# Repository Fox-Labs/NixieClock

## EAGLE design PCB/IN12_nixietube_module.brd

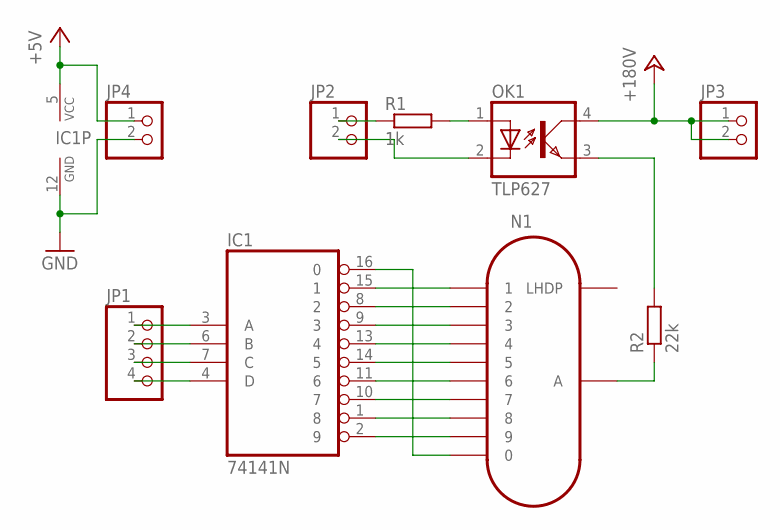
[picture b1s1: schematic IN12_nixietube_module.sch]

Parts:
IC1: 74141N; DIL16
JP1: PINHD-1X4; 1X04
JP2, JP3, JP4: PINHD-1X2; 1X02
N1: IN-12B; IN-12
OK1: TLP627; 4-SMD
R1: 1k; R0805
R2: 22k; 0207/10

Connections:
+5V: IC1.5 (VCC), JP4.1
+180V: JP3.1, JP3.2, OK1.4 (COL)
A: IC1.3 (A), JP1.1
B: IC1.6 (B), JP1.2
C: IC1.7 (C), JP1.3
C0: IC1.16 (0), N1.0
C1: IC1.15 (1), N1.1
C2: IC1.8 (2), N1.2
C3: IC1.9 (3), N1.3
C4: IC1.13 (4), N1.4
C5: IC1.14 (5), N1.5
C6: IC1.11 (6), N1.6
C7: IC1.10 (7), N1.7
C8: IC1.1 (8), N1.8
C9: IC1.2 (9), N1.9
D: IC1.4 (D), JP1.4
GND: IC1.12 (GND), JP4.2
LA: JP2.1, R1.1
LK: JP2.2, OK1.2 (C)
unnamed: N1.A, R2.1
unnamed: OK1.3 (EMIT), R2.2
unnamed: OK1.1 (A), R1.2

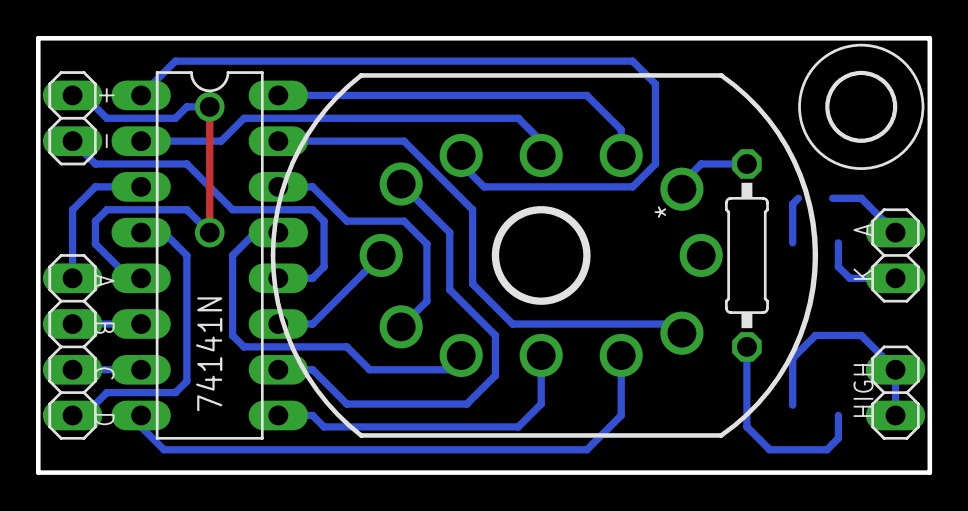
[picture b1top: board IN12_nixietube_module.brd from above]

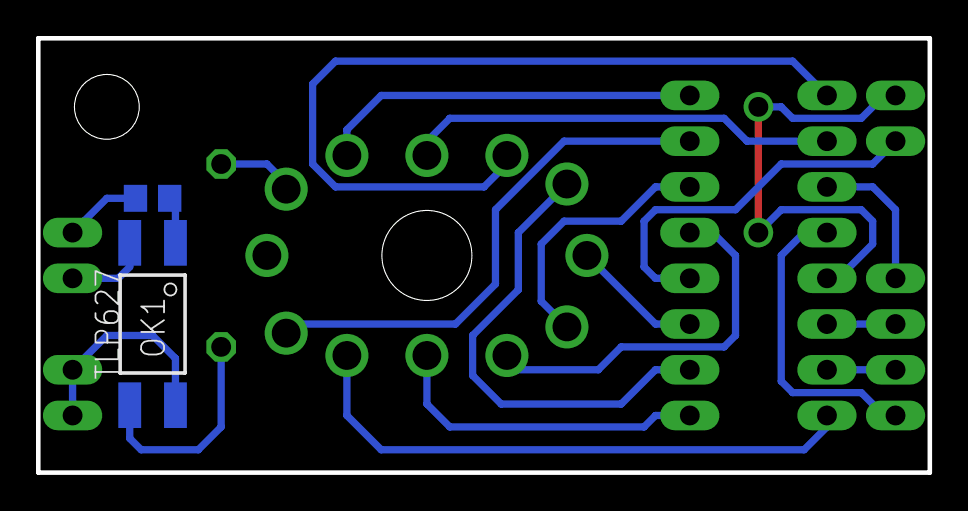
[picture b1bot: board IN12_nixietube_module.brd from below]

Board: 2 copper layers, 49.5 x 24.1 mm, 10 parts (2 on the bottom side), 22 nets.

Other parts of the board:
U$1: 3,6

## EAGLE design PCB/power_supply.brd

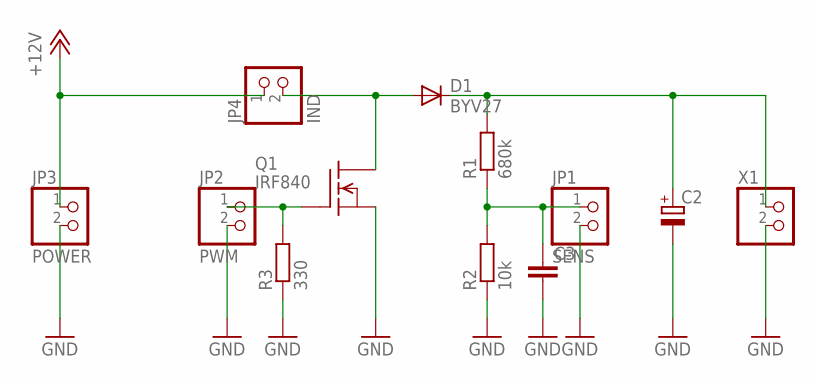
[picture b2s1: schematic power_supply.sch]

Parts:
C2: CPOL-EUE5-10,5; E5-10,5
C3: C-EU102-043X133; C102-043X133
D1: BYV27; SOD57
JP1: SENS; 1X02
JP2: PWM; 1X02
JP3: POWER; 1X02
JP4: IND; 1X02
Q1: IRF840; TO220-A
R1: 680k; 0207/7
R2: 10k; 0207/7
R3: 330; 0207/7
X1: W237-102

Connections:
180: C2.+, D1.C, R1.2, X1.1
+12V: JP3.1, JP4.1
GND: C2.-, C3.2, JP1.2, JP2.2, JP3.2, Q1.3 (S), R2.1, R3.1, X1.2
IND: D1.A, JP4.2, Q1.2 (D)
PWM: JP2.1, Q1.1 (G), R3.2
SENS: C3.1, JP1.1, R1.1, R2.2

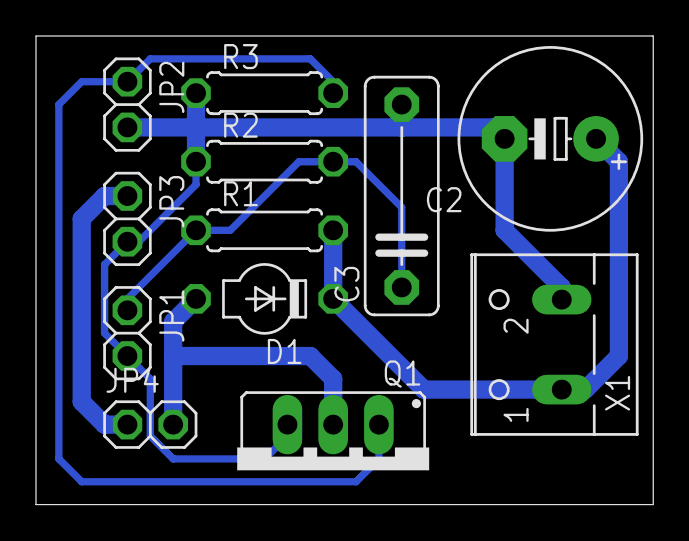
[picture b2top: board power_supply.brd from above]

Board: 2 copper layers, 34.3 x 26.0 mm, 12 parts (0 on the bottom side), 6 nets.

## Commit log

2018-05-13 - PCB and Firmware for a old nixie tube clock project. Not finished.
